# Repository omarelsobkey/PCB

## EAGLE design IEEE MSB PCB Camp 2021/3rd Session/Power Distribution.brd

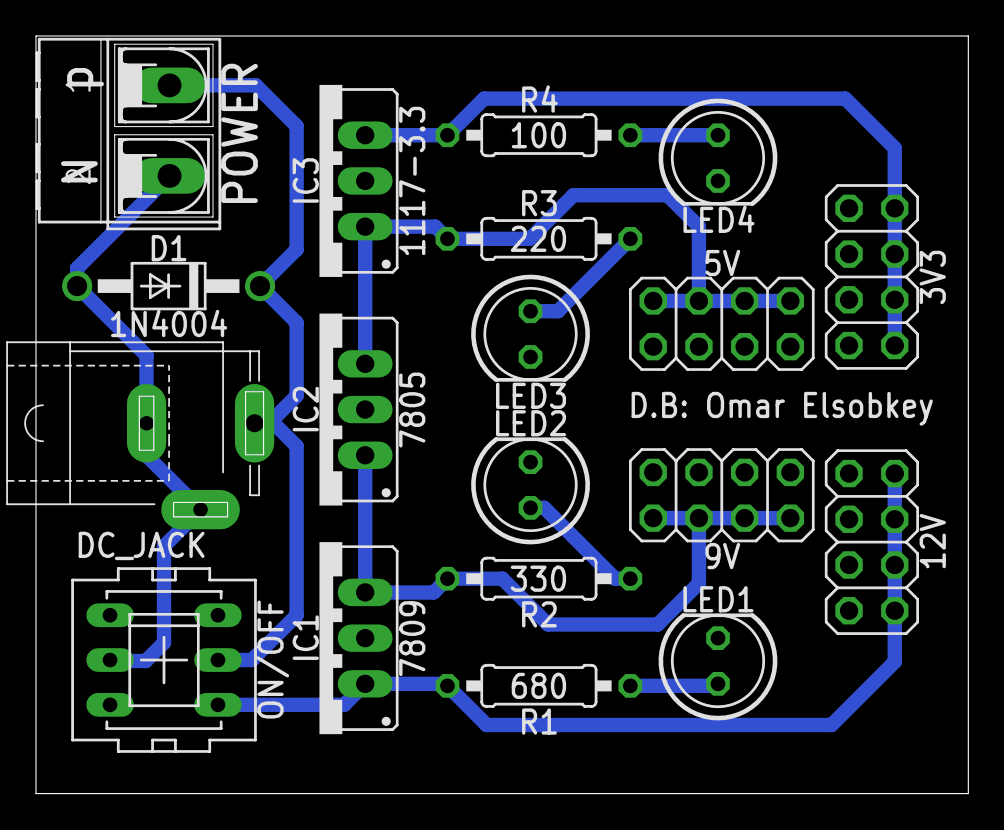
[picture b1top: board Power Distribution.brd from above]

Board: 2 copper layers, 51.8 x 42.1 mm, 19 parts (0 on the bottom side), 11 nets.

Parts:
3V3, 5V, 9V, 12V: 2X04
D1: 1N4004; DO41-10
DC_JACK: SPC4077
IC1: 7809; 78XXS
IC2: 7805; 78XXS
IC3: 1117-3.3; 78XXS
LED1, LED2, LED3, LED4: LED5MM
ON/OFF: PVA2R
POWER: AK500/2-H
R1: 680; 0207/10
R2: 330; 0207/10
R3: 220; 0207/10
R4: 100; 0207/10

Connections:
+: D1.C, DC_JACK.3, ON/OFF.2, POWER.1
+3V3: 3V3.2, 3V3.4, 3V3.6, 3V3.8, IC3.OUT, R4.2
+5V: 5V.2, 5V.4, 5V.6, 5V.8, IC2.OUT, IC3.IN, R3.2
+9V: 9V.2, 9V.4, 9V.6, 9V.8, IC1.OUT, IC2.IN, R2.2
+12V: 12V.2, 12V.4, 12V.6, 12V.8, IC1.IN, ON/OFF.1, R1.2
-: D1.A, DC_JACK.1, DC_JACK.2, ON/OFF.5, POWER.2
GND: 3V3.1, 3V3.3, 3V3.5, 3V3.7, 5V.1, 5V.3, 5V.5, 5V.7, 9V.1, 9V.3, 9V.5, 9V.7, 12V.1, 12V.3, 12V.5, 12V.7, IC1.GND, IC2.GND, IC3.GND, LED1.K, LED2.K, LED3.K, LED4.K, ON/OFF.4
unnamed: LED1.A, R1.1
unnamed: LED2.A, R2.1
unnamed: LED3.A, R3.1
unnamed: LED4.A, R4.1

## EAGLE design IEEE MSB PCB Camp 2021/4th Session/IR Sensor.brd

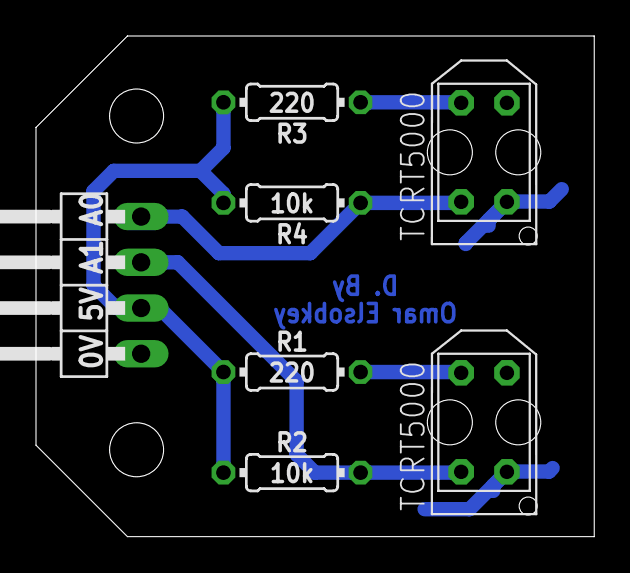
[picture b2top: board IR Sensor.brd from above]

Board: 2 copper layers, 31.0 x 27.8 mm, 7 parts (0 on the bottom side), 6 nets.

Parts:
JP1: 1X04/90
R1, R3: 220; 0204/7
R2, R4: 10k; 0204/7
SENS-1, SENS-2: TCRT5000; 5000

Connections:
+5V: JP1.2, R1.2, R2.2, R3.2, R4.2
A0: JP1.4, R4.1, SENS-2.P$1
A1: JP1.3, R2.1, SENS-1.P$1
GND: JP1.1, SENS-1.P$2, SENS-1.P$4, SENS-2.P$2, SENS-2.P$4
unnamed: R1.1, SENS-1.P$3
unnamed: R3.1, SENS-2.P$3

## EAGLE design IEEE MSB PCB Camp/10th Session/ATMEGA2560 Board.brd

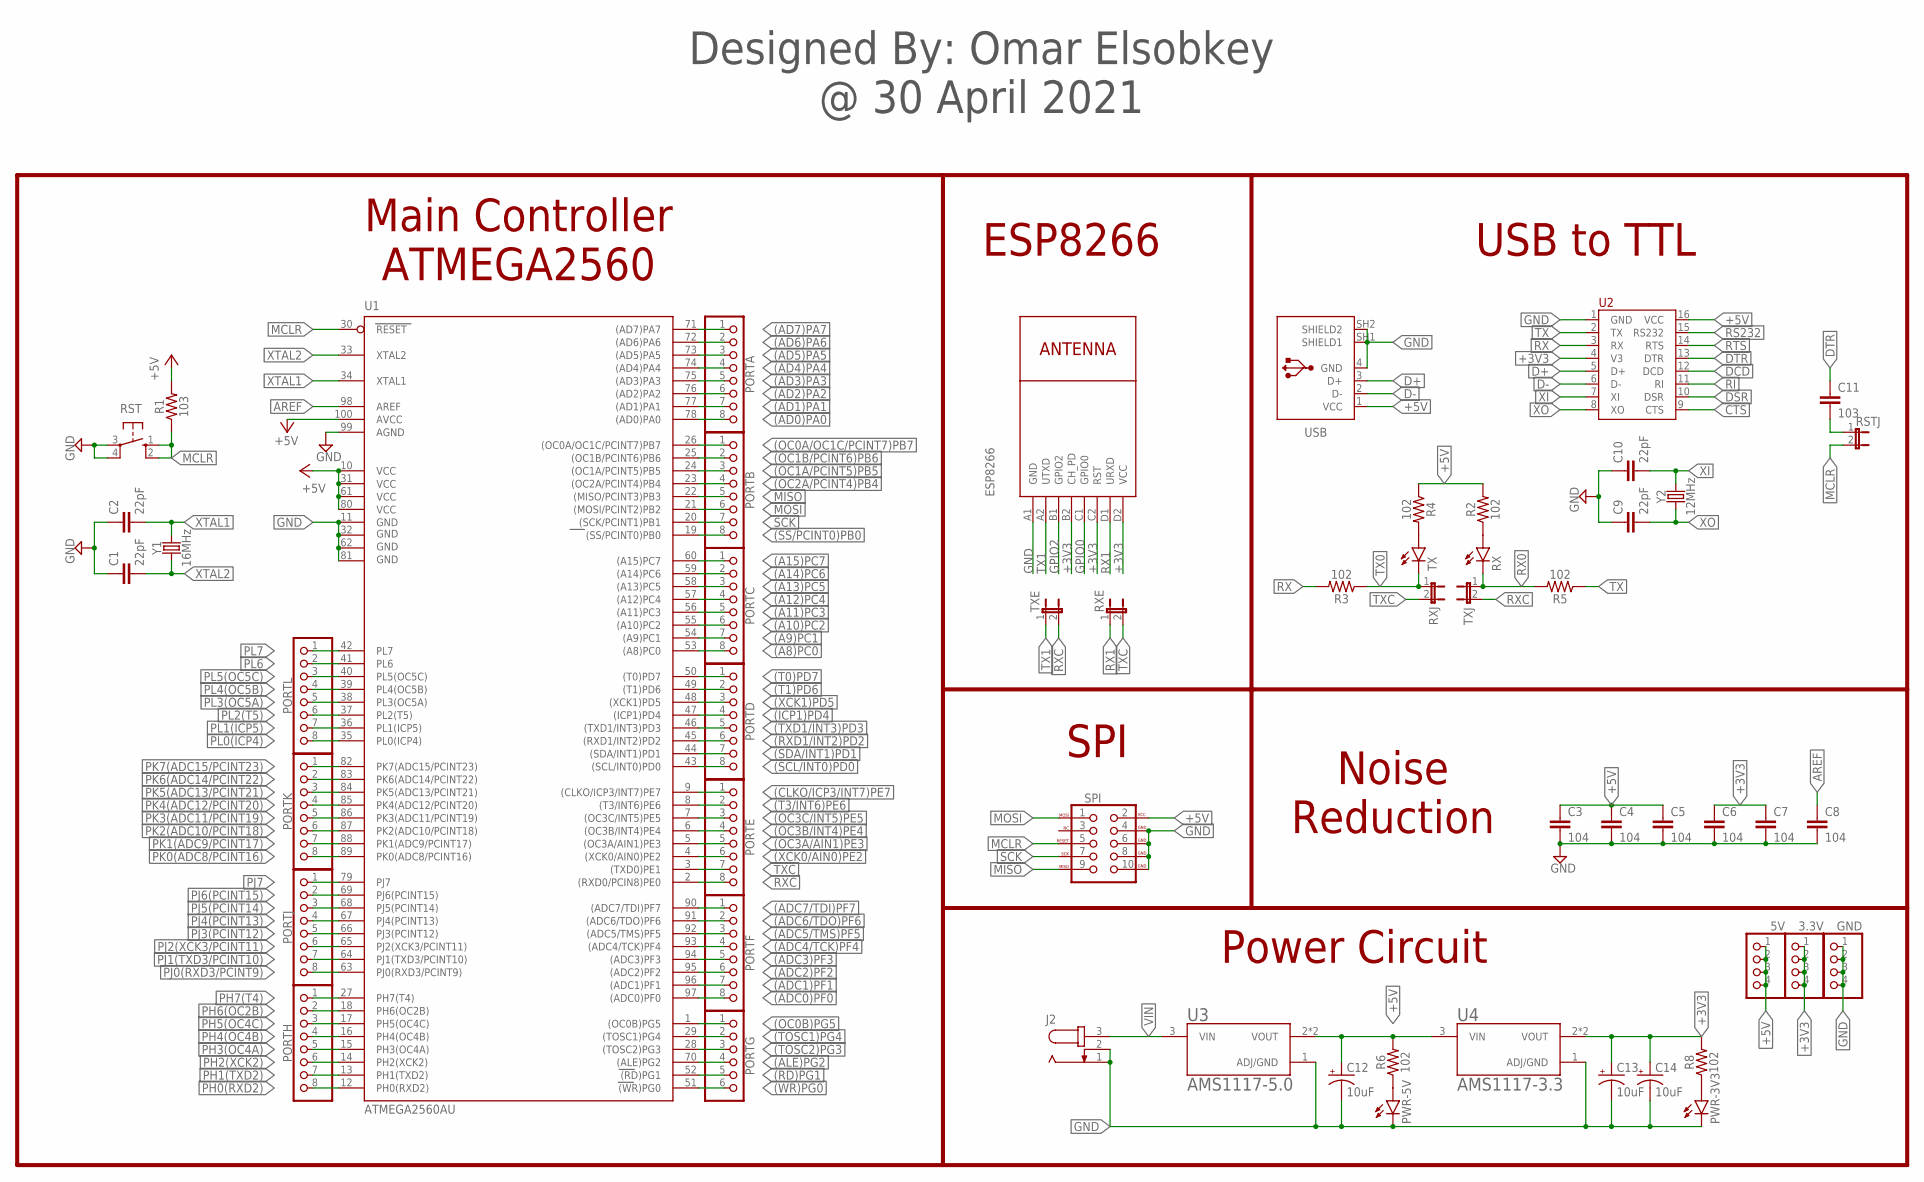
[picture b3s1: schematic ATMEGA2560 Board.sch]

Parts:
3.3V, 5V: PINHD-1X4; 1X04
C1, C2, C9, C10: 22pF; CAP-PTH-2.54
C3, C4, C5, C6, C7, C8: 104; CAP-PTH-2.54
C11: 103; CAP-PTH-2.54
C12, C13, C14: 10uF; CPOL-RADIAL-2.5MM-5MM-KIT
ESP8266: WIRELESS-WIFI-ESP-01
GND: PINHD-1X4; 1X04
J2: JACK-PLUG0; SPC4077
PORTA: PINHD-1X8; 1X08
PORTB: PINHD-1X8; 1X08
PORTC: PINHD-1X8; 1X08
PORTD: PINHD-1X8; 1X08
PORTE: PINHD-1X8; 1X08
PORTF: PINHD-1X8; 1X08
PORTG: PINHD-1X6; 1X06
PORTH: PINHD-1X8; 1X08
PORTJ: PINHD-1X8; 1X08
PORTK: PINHD-1X8; 1X08
PORTL: PINHD-1X8; 1X08
PWR-3V3, PWR-5V: LEDCHIP-LED0805; CHIP-LED0805
R1: 103; 1206
R2, R3, R4, R5, R6, R8: 102; 1206
RST: 10-XX; B3F-10XX
RSTJ: JP1E; JP1
RX: LEDCHIP-LED0805; CHIP-LED0805
RXE: JP1E; JP1
RXJ: JP1E; JP1
SPI: AVR_SPI_PROG_5X2LOCK; 2X5-SHROUDED_LOCK
TX: LEDCHIP-LED0805; CHIP-LED0805
TXE: JP1E; JP1
TXJ: JP1E; JP1
U1: ATMEGA2560AU; TQFP100
U2: CH340G; SOP-16
U3: AMS1117-5.0
U4: AMS1117-3.3; AMS1117-5.0
USB: 61729-1011; 61729-1011BLF
Y1: 16MHz; HC49U
Y2: 12MHz; HC49U

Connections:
(A8)PC0: PORTC.8, U1.53 ((A8)PC0)
(A9)PC1: PORTC.7, U1.54 ((A9)PC1)
(A10)PC2: PORTC.6, U1.55 ((A10)PC2)
(A11)PC3: PORTC.5, U1.56 ((A11)PC3)
(A12)PC4: PORTC.4, U1.57 ((A12)PC4)
(A13)PC5: PORTC.3, U1.58 ((A13)PC5)
(A14)PC6: PORTC.2, U1.59 ((A14)PC6)
(A15)PC7: PORTC.1, U1.60 ((A15)PC7)
(AD0)PA0: PORTA.8, U1.78 ((AD0)PA0)
(AD1)PA1: PORTA.7, U1.77 ((AD1)PA1)
(AD2)PA2: PORTA.6, U1.76 ((AD2)PA2)
(AD3)PA3: PORTA.5, U1.75 ((AD3)PA3)
(AD4)PA4: PORTA.4, U1.74 ((AD4)PA4)
(AD5)PA5: PORTA.3, U1.73 ((AD5)PA5)
(AD6)PA6: PORTA.2, U1.72 ((AD6)PA6)
(AD7)PA7: PORTA.1, U1.71 ((AD7)PA7)
(ADC0)PF0: PORTF.8, U1.97 ((ADC0)PF0)
(ADC1)PF1: PORTF.7, U1.96 ((ADC1)PF1)
(ADC2)PF2: PORTF.6, U1.95 ((ADC2)PF2)
(ADC3)PF3: PORTF.5, U1.94 ((ADC3)PF3)
(ADC4/TCK)PF4: PORTF.4, U1.93 ((ADC4/TCK)PF4)
(ADC5/TMS)PF5: PORTF.3, U1.92 ((ADC5/TMS)PF5)
(ADC6/TDO)PF6: PORTF.2, U1.91 ((ADC6/TDO)PF6)
(ADC7/TDI)PF7: PORTF.1, U1.90 ((ADC7/TDI)PF7)
(ALE)PG2: PORTG.4, U1.70 ((ALE)PG2)
(CLKO/ICP3/INT7)PE7: PORTE.1, U1.9 ((CLKO/ICP3/INT7)PE7)
(ICP1)PD4: PORTD.4, U1.47 ((ICP1)PD4)
(OC0A/OC1C/PCINT7)PB7: PORTB.1, U1.26 ((OC0A/OC1C/PCINT7)PB7)
(OC0B)PG5: PORTG.1, U1.1 ((OC0B)PG5)
(OC1A/PCINT5)PB5: PORTB.3, U1.24 ((OC1A/PCINT5)PB5)
(OC1B/PCINT6)PB6: PORTB.2, U1.25 ((OC1B/PCINT6)PB6)
(OC2A/PCINT4)PB4: PORTB.4, U1.23 ((OC2A/PCINT4)PB4)
(OC3A/AIN1)PE3: PORTE.5, U1.5 ((OC3A/AIN1)PE3)
(OC3B/INT4)PE4: PORTE.4, U1.6 ((OC3B/INT4)PE4)
(OC3C/INT5)PE5: PORTE.3, U1.7 ((OC3C/INT5)PE5)
(RD)PG1: PORTG.5, U1.52 ((RD)PG1)
(RXD1/INT2)PD2: PORTD.6, U1.45 ((RXD1/INT2)PD2)
(SCL/INT0)PD0: PORTD.8, U1.43 ((SCL/INT0)PD0)
(SDA/INT1)PD1: PORTD.7, U1.44 ((SDA/INT1)PD1)
(SS/PCINT0)PB0: PORTB.8, U1.19 ((SS/PCINT0)PB0)
(T0)PD7: PORTD.1, U1.50 ((T0)PD7)
(T1)PD6: PORTD.2, U1.49 ((T1)PD6)
(T3/INT6)PE6: PORTE.2, U1.8 ((T3/INT6)PE6)
(TOSC1)PG4: PORTG.2, U1.29 ((TOSC1)PG4)
(TOSC2)PG3: PORTG.3, U1.28 ((TOSC2)PG3)
(TXD1/INT3)PD3: PORTD.5, U1.46 ((TXD1/INT3)PD3)
(WR)PG0: PORTG.6, U1.51 ((WR)PG0)
(XCK0/AIN0)PE2: PORTE.6, U1.4 ((XCK0/AIN0)PE2)
(XCK1)PD5: PORTD.3, U1.48 ((XCK1)PD5)
+3V3: 3.3V.1, 3.3V.2, 3.3V.3, 3.3V.4, C6.1, C7.1, C13.1 (+), C14.1 (+), ESP8266.B2 (CH_PD), ESP8266.C2 (RST), ESP8266.D2 (VCC), R8.2, U2.4 (V3), U4.2 (VOUT), U4.4 (VOUT)
+5V: 5V.1, 5V.2, 5V.3, 5V.4, C3.1, C4.1, C5.1, C12.1 (+), R1.2, R2.2, R4.1, R6.2, SPI.2 (VCC), U1.10 (VCC), U1.31 (VCC1), U1.61 (VCC2), U1.80 (VCC3), U1.100 (AVCC), U2.16 (VCC), U3.2 (VOUT), U3.4 (VOUT), U4.3 (VIN), USB.1 (VCC)
AREF: C8.1, U1.98 (AREF)
CTS: U2.9 (CTS)
D+: U2.5 (D+), USB.3 (D+)
D-: U2.6 (D-), USB.2 (D-)
DCD: U2.12 (DCD)
DSR: U2.10 (DSR)
DTR: C11.1, U2.13 (DTR)
GND: C1.1, C2.1, C3.2, C4.2, C5.2, C6.2, C7.2, C8.2, C9.1, C10.1, C12.2 (-), C13.2 (-), C14.2 (-), ESP8266.A1 (GND), GND.1, GND.2, GND.3, GND.4, J2.1, J2.2, PWR-3V3.C, PWR-5V.C, RST.3, RST.4 (P1), SPI.4 (GND), SPI.6 (GND), SPI.8 (GND), SPI.10 (GND), U1.11 (GND), U1.32 (GND1), U1.62 (GND2), U1.81 (GND3), U1.99 (AGND), U2.1 (GND), U3.1 (ADJ/GND), U4.1 (ADJ/GND), USB.4 (GND), USB.SH1 (SHIELD1), USB.SH2 (SHIELD2)
GPIO0: ESP8266.C1 (GPIO0)
GPIO2: ESP8266.B1 (GPIO2)
MCLR: R1.1, RST.1 (S), RST.2 (S1), RSTJ.2, SPI.5 (RESET), U1.30 (RESET)
MISO: PORTB.5, SPI.9 (MISO), U1.22 ((MISO/PCINT3)PB3)
MOSI: PORTB.6, SPI.1 (MOSI), U1.21 ((MOSI/PCINT2)PB2)
unnamed: R2.1, RX.A
unnamed: R4.2, TX.A
unnamed: PWR-5V.A, R6.1
unnamed: PWR-3V3.A, R8.1
unnamed: C11.2, RSTJ.1
PH0(RXD2): PORTH.8, U1.12 (PH0(RXD2))
PH1(TXD2): PORTH.7, U1.13 (PH1(TXD2))
PH2(XCK2): PORTH.6, U1.14 (PH2(XCK2))
PH3(OC4A): PORTH.5, U1.15 (PH3(OC4A))
PH4(OC4B): PORTH.4, U1.16 (PH4(OC4B))
PH5(OC4C): PORTH.3, U1.17 (PH5(OC4C))
PH6(OC2B): PORTH.2, U1.18 (PH6(OC2B))
PH7(T4): PORTH.1, U1.27 (PH7(T4))
PJ0(RXD3/PCINT9): PORTJ.8, U1.63 (PJ0(RXD3/PCINT9))
PJ1(TXD3/PCINT10): PORTJ.7, U1.64 (PJ1(TXD3/PCINT10))
PJ2(XCK3/PCINT11): PORTJ.6, U1.65 (PJ2(XCK3/PCINT11))
PJ3(PCINT12): PORTJ.5, U1.66 (PJ3(PCINT12))
PJ4(PCINT13): PORTJ.4, U1.67 (PJ4(PCINT13))
PJ5(PCINT14): PORTJ.3, U1.68 (PJ5(PCINT14))
PJ6(PCINT15): PORTJ.2, U1.69 (PJ6(PCINT15))
PJ7: PORTJ.1, U1.79 (PJ7)
PK0(ADC8/PCINT16): PORTK.8, U1.89 (PK0(ADC8/PCINT16))
PK1(ADC9/PCINT17): PORTK.7, U1.88 (PK1(ADC9/PCINT17))
PK2(ADC10/PCINT18): PORTK.6, U1.87 (PK2(ADC10/PCINT18))
PK3(ADC11/PCINT19): PORTK.5, U1.86 (PK3(ADC11/PCINT19))
PK4(ADC12/PCINT20): PORTK.4, U1.85 (PK4(ADC12/PCINT20))
PK5(ADC13/PCINT21): PORTK.3, U1.84 (PK5(ADC13/PCINT21))
PK6(ADC14/PCINT22): PORTK.2, U1.83 (PK6(ADC14/PCINT22))
PK7(ADC15/PCINT23): PORTK.1, U1.82 (PK7(ADC15/PCINT23))
PL0(ICP4): PORTL.8, U1.35 (PL0(ICP4))
PL1(ICP5): PORTL.7, U1.36 (PL1(ICP5))
PL2(T5): PORTL.6, U1.37 (PL2(T5))
PL3(OC5A): PORTL.5, U1.38 (PL3(OC5A))
PL4(OC5B): PORTL.4, U1.39 (PL4(OC5B))
PL5(OC5C): PORTL.3, U1.40 (PL5(OC5C))
PL6: PORTL.2, U1.41 (PL6)
PL7: PORTL.1, U1.42 (PL7)
RI: U2.11 (RI)
RS232: U2.15 (RS232)
RTS: U2.14 (RTS)
RX: R3.2, U2.3 (RX)
RX0: R5.2, RX.C, TXJ.1
RX1: ESP8266.D1 (URXD), RXE.1
RXC: PORTE.8, TXE.2, TXJ.2, U1.2 ((RXD0/PCIN8)PE0)
SCK: PORTB.7, SPI.7 (SCK), U1.20 ((SCK/PCINT1)PB1)
TX: R5.1, U2.2 (TX)
TX0: R3.1, RXJ.1, TX.C
TX1: ESP8266.A2 (UTXD), TXE.1
TXC: PORTE.7, RXE.2, RXJ.2, U1.3 ((TXD0)PE1)
VIN: J2.3, U3.3 (VIN)
XI: C10.2, U2.7 (XI), Y2.2
XO: C9.2, U2.8 (XO), Y2.1
XTAL1: C2.2, U1.34 (XTAL1), Y1.2
XTAL2: C1.2, U1.33 (XTAL2), Y1.1

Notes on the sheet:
Main Controller ATMEGA2560
ESP8266
USB to TTL
SPI
Noise Reduction
Power Circuit
Designed By: Omar Elsobkey @ 30 April 2021

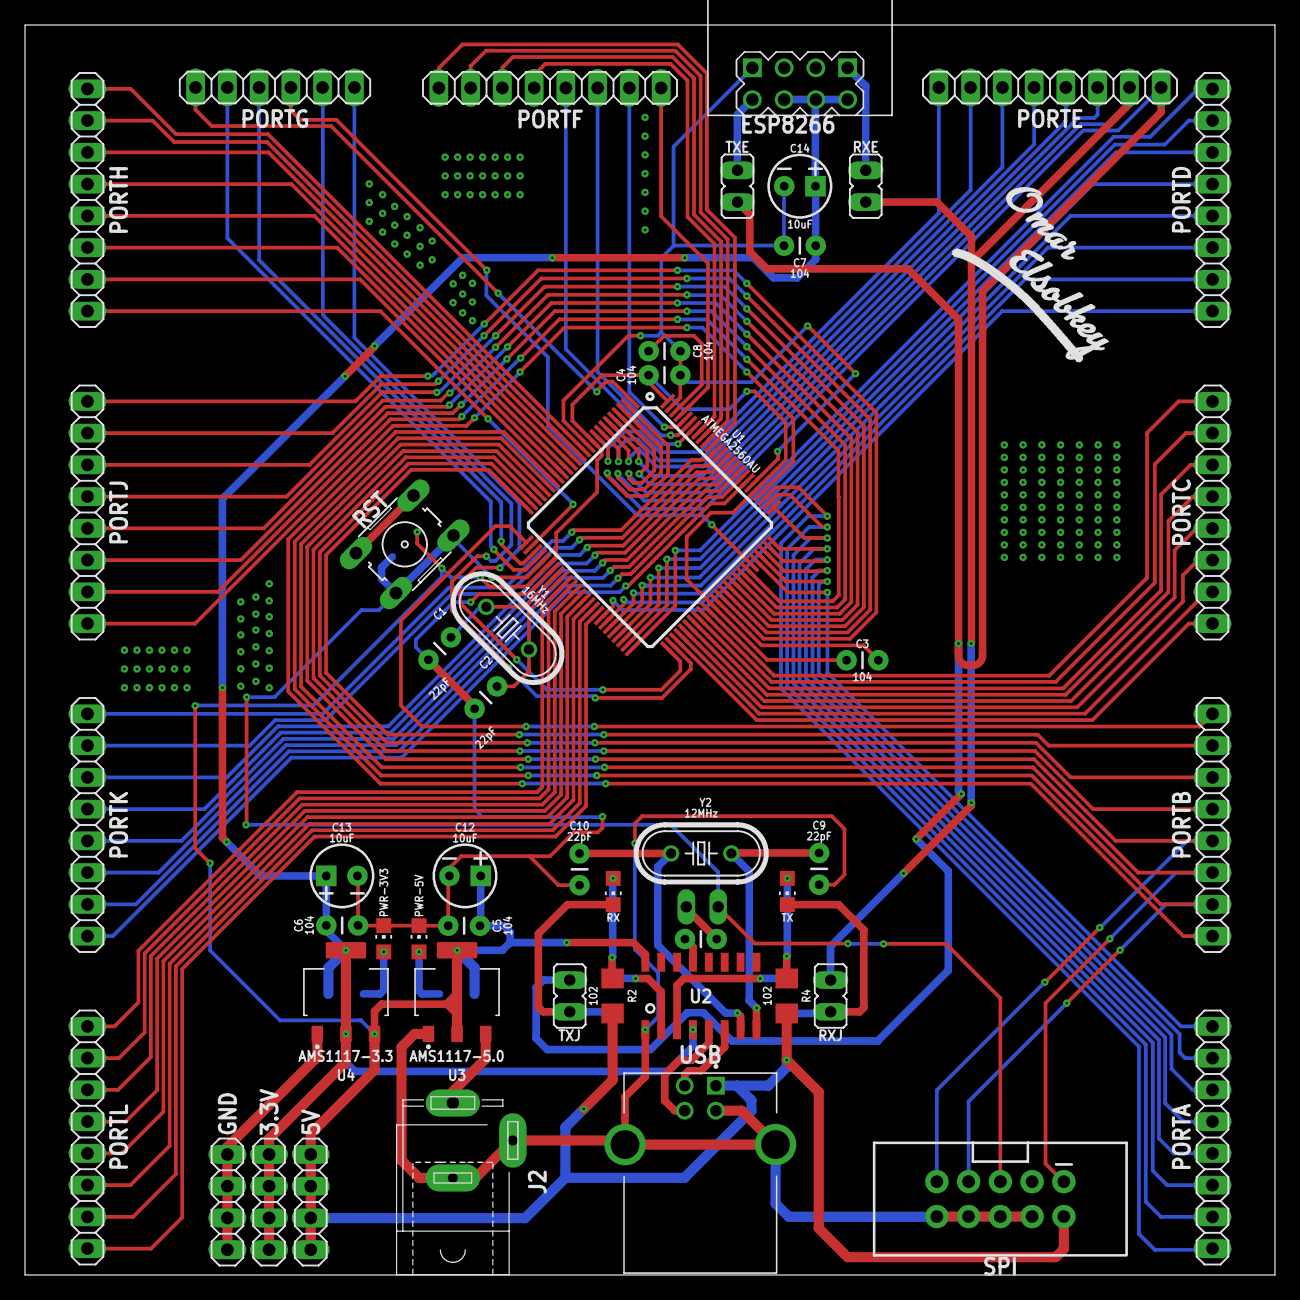
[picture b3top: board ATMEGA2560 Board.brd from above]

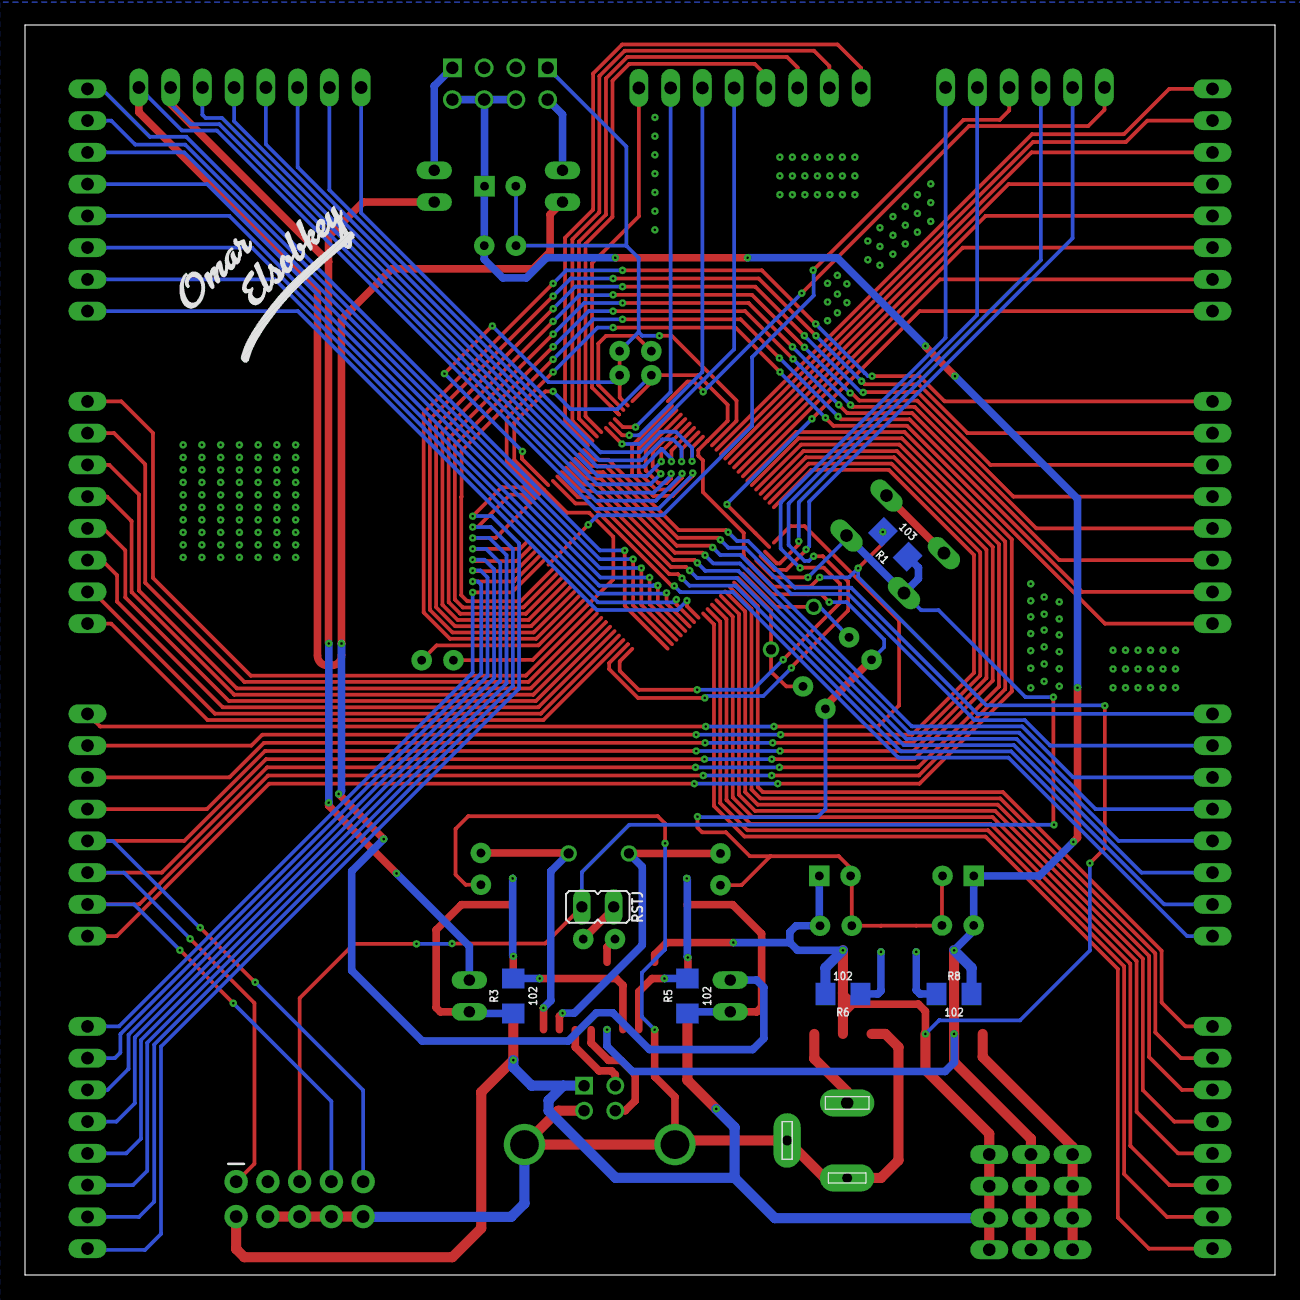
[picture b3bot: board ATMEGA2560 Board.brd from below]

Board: 2 copper layers, 100.0 x 100.0 mm, 57 parts (7 on the bottom side), 110 nets.

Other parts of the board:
U$1, U$2: OMAR_ELSOBKEY_X1

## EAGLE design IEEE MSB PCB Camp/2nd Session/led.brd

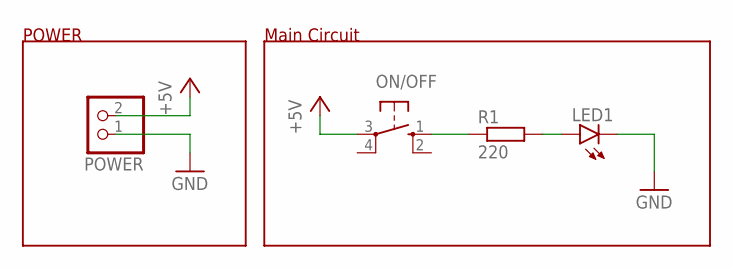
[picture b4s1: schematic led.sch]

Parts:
LED1: LED3MM
ON/OFF: 10-XX; B3F-10XX
POWER: PINHD-1X2; 1X02
R1: 220; 0204/7

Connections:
+5V: ON/OFF.3, POWER.2
GND: LED1.K (C), POWER.1
unnamed: ON/OFF.1 (S), R1.1
unnamed: LED1.A, R1.2

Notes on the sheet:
POWER
Main Circuit

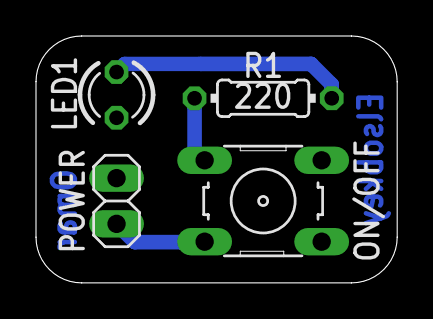
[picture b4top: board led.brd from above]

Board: 2 copper layers, 20.1 x 13.7 mm, 4 parts (0 on the bottom side), 4 nets.

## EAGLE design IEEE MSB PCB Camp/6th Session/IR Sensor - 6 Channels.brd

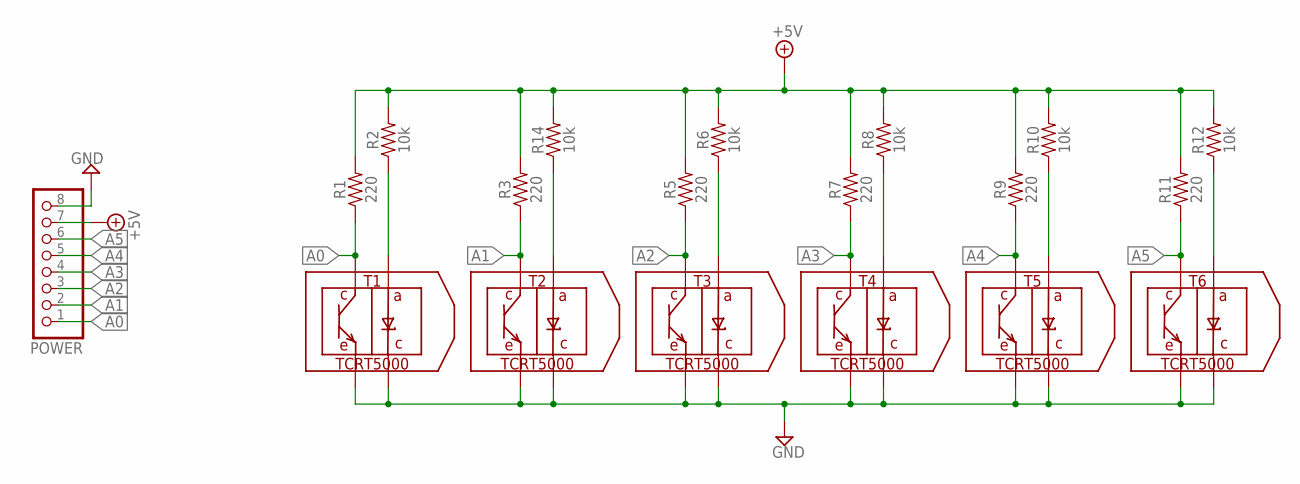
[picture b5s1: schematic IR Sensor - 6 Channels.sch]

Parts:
POWER: PINHD-1X8/90; 1X08/90
R1, R3, R5, R7, R9, R11: 220; 1206
R2, R6, R8, R10, R12, R14: 10k; 1206
T1, T2, T3, T4, T5, T6: TCRT5000; 5000

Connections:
+5V: POWER.7, R1.2, R2.2, R3.2, R5.2, R6.2, R7.2, R8.2, R9.2, R10.2, R11.2, R12.2, R14.2
A0: POWER.1, R1.1, T1.P$1
A1: POWER.2, R3.1, T2.P$1
A2: POWER.3, R5.1, T3.P$1
A3: POWER.4, R7.1, T4.P$1
A4: POWER.5, R9.1, T5.P$1
A5: POWER.6, R11.1, T6.P$1
GND: POWER.8, T1.P$2, T1.P$4, T2.P$2, T2.P$4, T3.P$2, T3.P$4, T4.P$2, T4.P$4, T5.P$2, T5.P$4, T6.P$2, T6.P$4
unnamed: R2.1, T1.P$3
unnamed: R14.1, T2.P$3
unnamed: R6.1, T3.P$3
unnamed: R12.1, T6.P$3
unnamed: R10.1, T5.P$3
unnamed: R8.1, T4.P$3

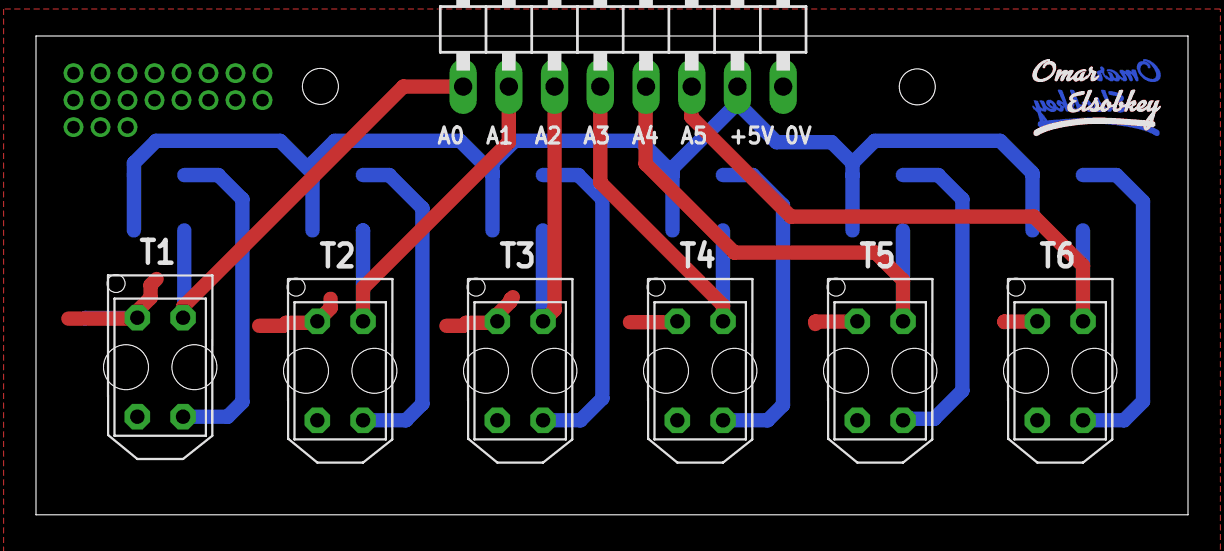
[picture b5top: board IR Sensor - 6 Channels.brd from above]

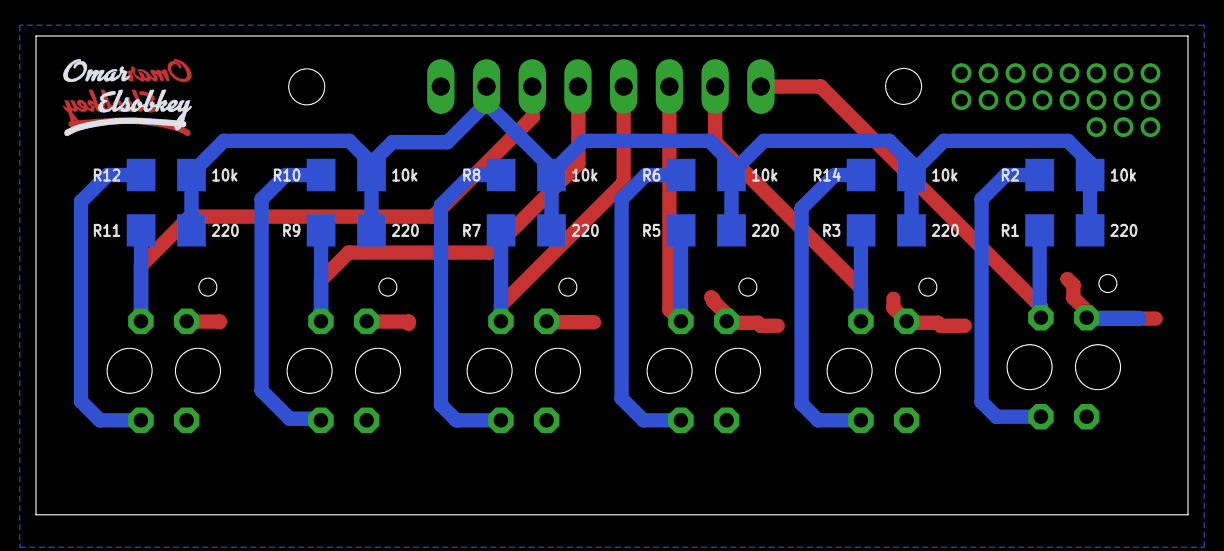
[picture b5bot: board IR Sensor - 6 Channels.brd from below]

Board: 2 copper layers, 64.0 x 26.6 mm, 23 parts (14 on the bottom side), 14 nets.

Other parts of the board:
U$1, U$2: OMAR_ELSOBKEY_X0.5_T
U$3, U$4: OMAR_ELSOBKEY_X0.5_TN

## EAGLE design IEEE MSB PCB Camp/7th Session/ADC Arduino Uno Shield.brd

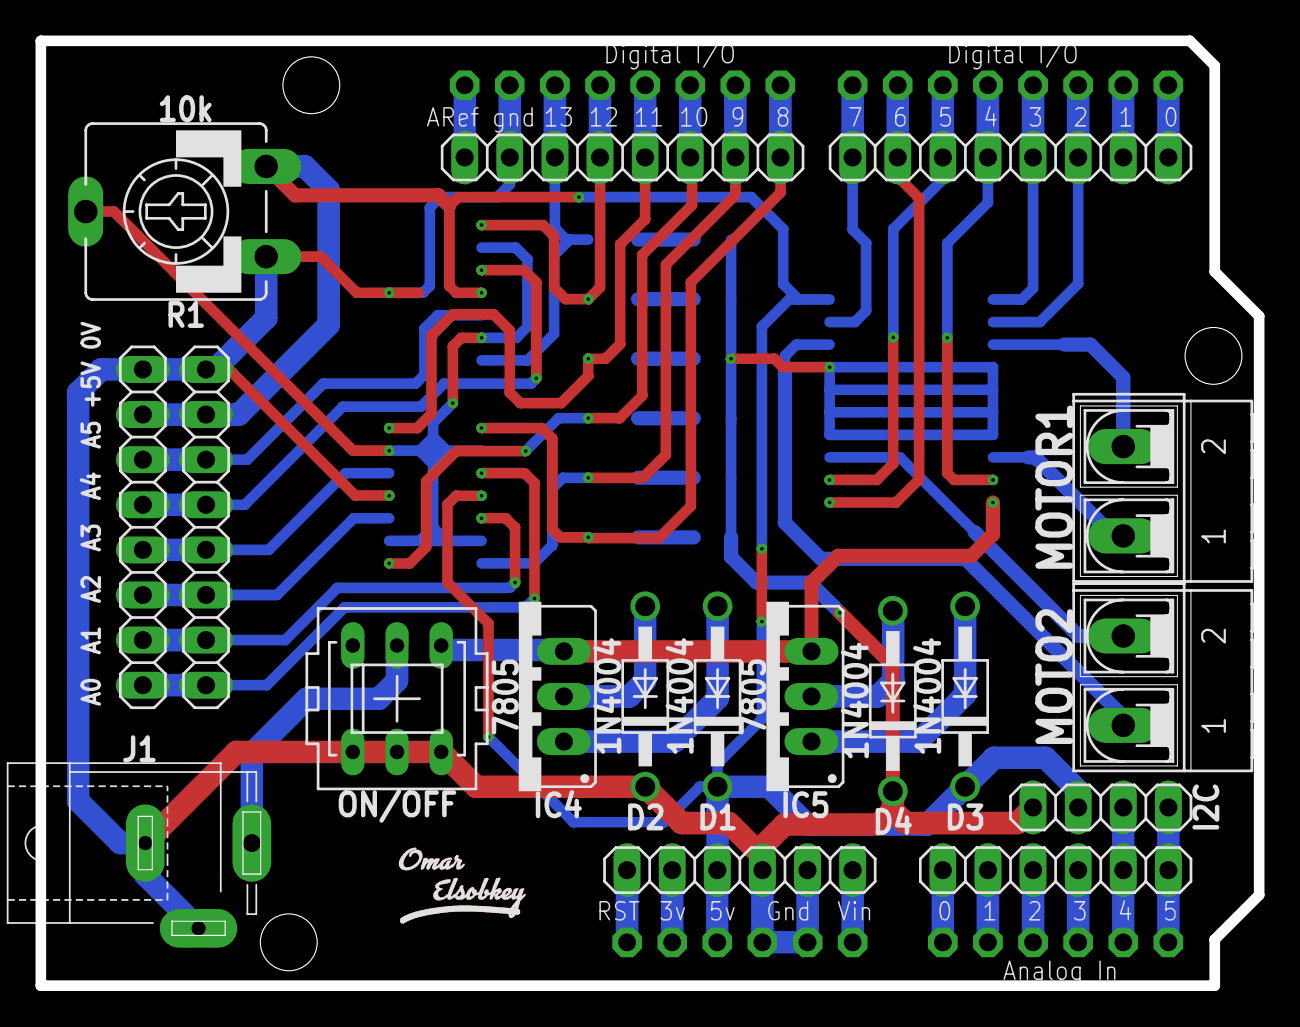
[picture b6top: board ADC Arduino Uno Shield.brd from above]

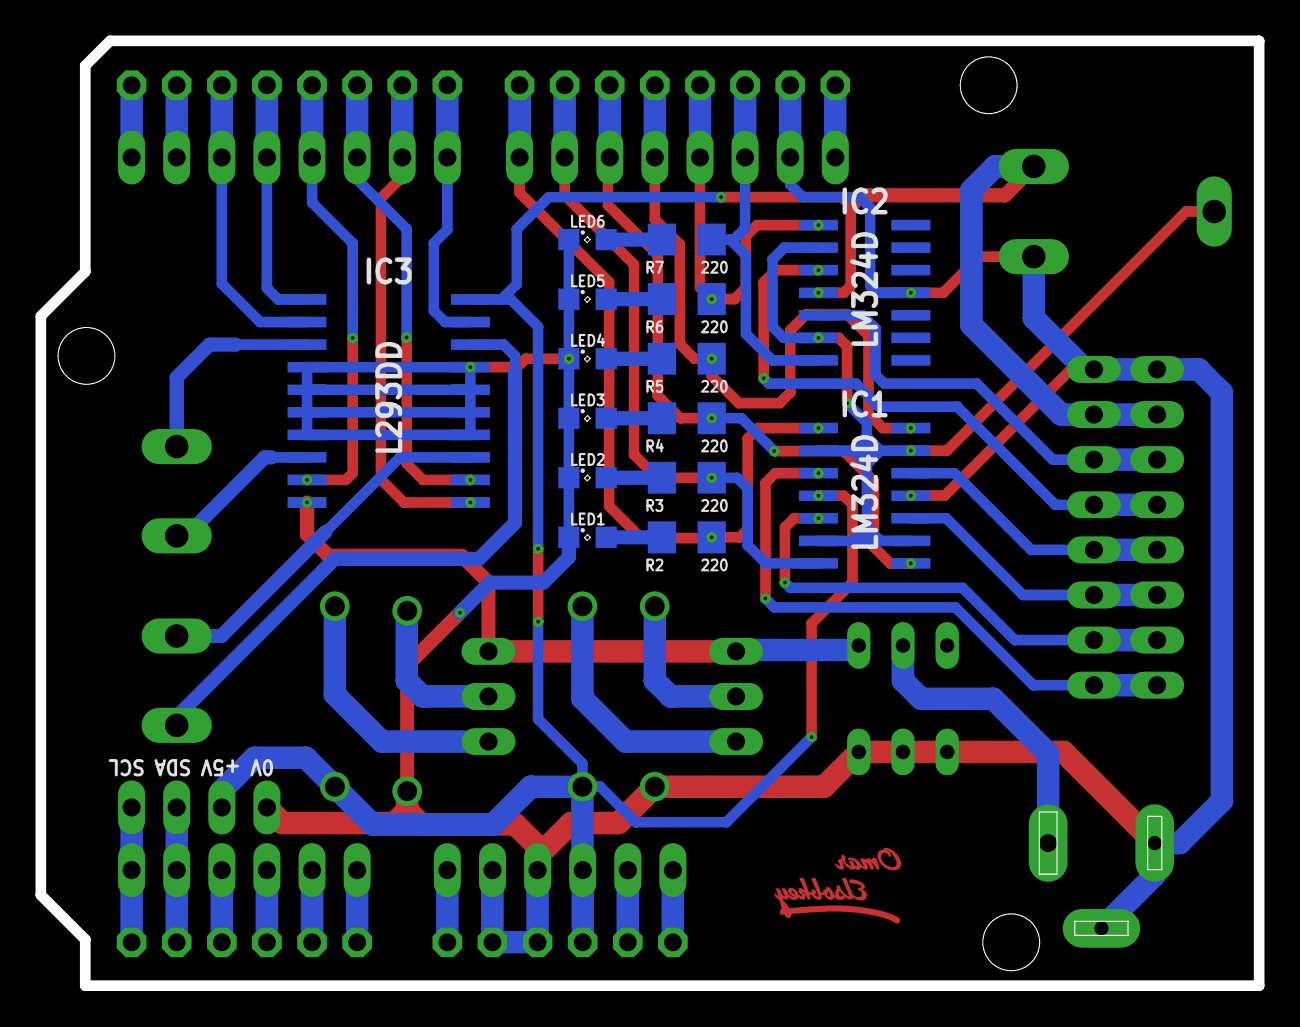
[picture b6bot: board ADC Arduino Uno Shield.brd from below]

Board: 2 copper layers, 68.6 x 53.2 mm, 35 parts (15 on the bottom side), 49 nets.

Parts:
CON1, CON2: 1X08
D1, D2, D3, D4: 1N4004; DO41-10
I2C: 1X04
IC1, IC2: LM324D; SO14
IC3: L293DD; SO20
IC4, IC5: 7805; 78XXS
J1: SPC4077
JP1, JP2: 1X06
JP3, JP4: 1X08
LED1, LED2, LED3, LED4, LED5, LED6: SML0805
MOTO2: AK500/2-H
MOTOR1: AK500/2-H
ON/OFF: PVA2R
R1: 10k; CA9V
R2, R3, R4, R5, R6, R7: 220; 1206
U$2: ARDUINO-NODIM
U$3: OMAR_ELSOBKEY_X0.5

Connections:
2: IC3.2, JP3.6, U$2.D2
3: IC3.1, JP3.5, U$2.D3
4: IC3.9, JP3.4, U$2.D4
5: IC3.12, JP3.3, U$2.D5
6: IC3.11, JP3.2, U$2.D6
7: IC3.19, JP3.1, U$2.D7
+5V: CON1.7, CON2.7, D1.C, D3.C, I2C.3, IC1.4, IC2.4, IC3.20, JP2.4, R1.E, U$2.5V
+12V: IC3.10, IC4.OUT, IC5.OUT, ON/OFF.1
A0: CON1.1, CON2.1, IC1.3
A1: CON1.2, CON2.2, IC1.5
A2: CON1.3, CON2.3, IC1.10
A3: CON1.4, CON2.4, IC1.12
A4: CON1.5, CON2.5, IC2.3
A5: CON1.6, CON2.6, IC2.5
D0: IC1.1, JP4.8, R2.2, U$2.D8
D1: IC1.7, JP4.7, R3.2, U$2.D9
D2: IC1.8, JP4.6, R4.2, U$2.D10
D3: IC1.14, JP4.5, R5.2, U$2.D11
D4: IC2.1, JP4.4, R6.2, U$2.D12
D5: IC2.7, JP4.3, R7.2, U$2.D13
GND: CON1.8, CON2.8, D2.C, D4.C, I2C.4, IC1.11, IC2.11, IC3.4, IC3.5, IC3.6, IC3.7, IC3.14, IC3.15, IC3.16, IC3.17, J1.1, J1.2, JP2.2, JP2.3, JP4.2, LED1.C, LED2.C, LED3.C, LED4.C, LED5.C, LED6.C, ON/OFF.4, ON/OFF.5, ON/OFF.6, R1.A, U$2.GND, U$2.GND1, U$2.GND2
unnamed: D1.A, IC4.IN
unnamed: JP1.3, U$2.A3
unnamed: D2.A, IC4.GND
unnamed: D3.A, IC5.IN
unnamed: D4.A, IC5.GND
unnamed: JP1.4, U$2.A2
unnamed: LED1.A, R2.1
unnamed: LED2.A, R3.1
unnamed: LED3.A, R4.1
unnamed: LED4.A, R5.1
unnamed: LED5.A, R6.1
unnamed: LED6.A, R7.1
unnamed: IC1.2, IC1.6, IC1.9, IC1.13, IC2.2, IC2.6, R1.S
unnamed: JP1.5, U$2.A1
unnamed: IC3.3, MOTOR1.2
unnamed: IC3.8, MOTOR1.1
unnamed: IC3.13, MOTO2.2
unnamed: IC3.18, MOTO2.1
unnamed: JP1.6, U$2.A0
unnamed: JP4.1, U$2.AREF
unnamed: JP3.7, U$2.D1
unnamed: JP3.8, U$2.D0
POWER: J1.3, ON/OFF.2
SCL: I2C.1, JP1.1, U$2.A5
SDA: I2C.2, JP1.2, U$2.A4
U$2_3V: JP2.5, U$2.3V
U$2_/RESET: JP2.6, U$2.RESET
U$2_VIN: JP2.1, U$2.VIN

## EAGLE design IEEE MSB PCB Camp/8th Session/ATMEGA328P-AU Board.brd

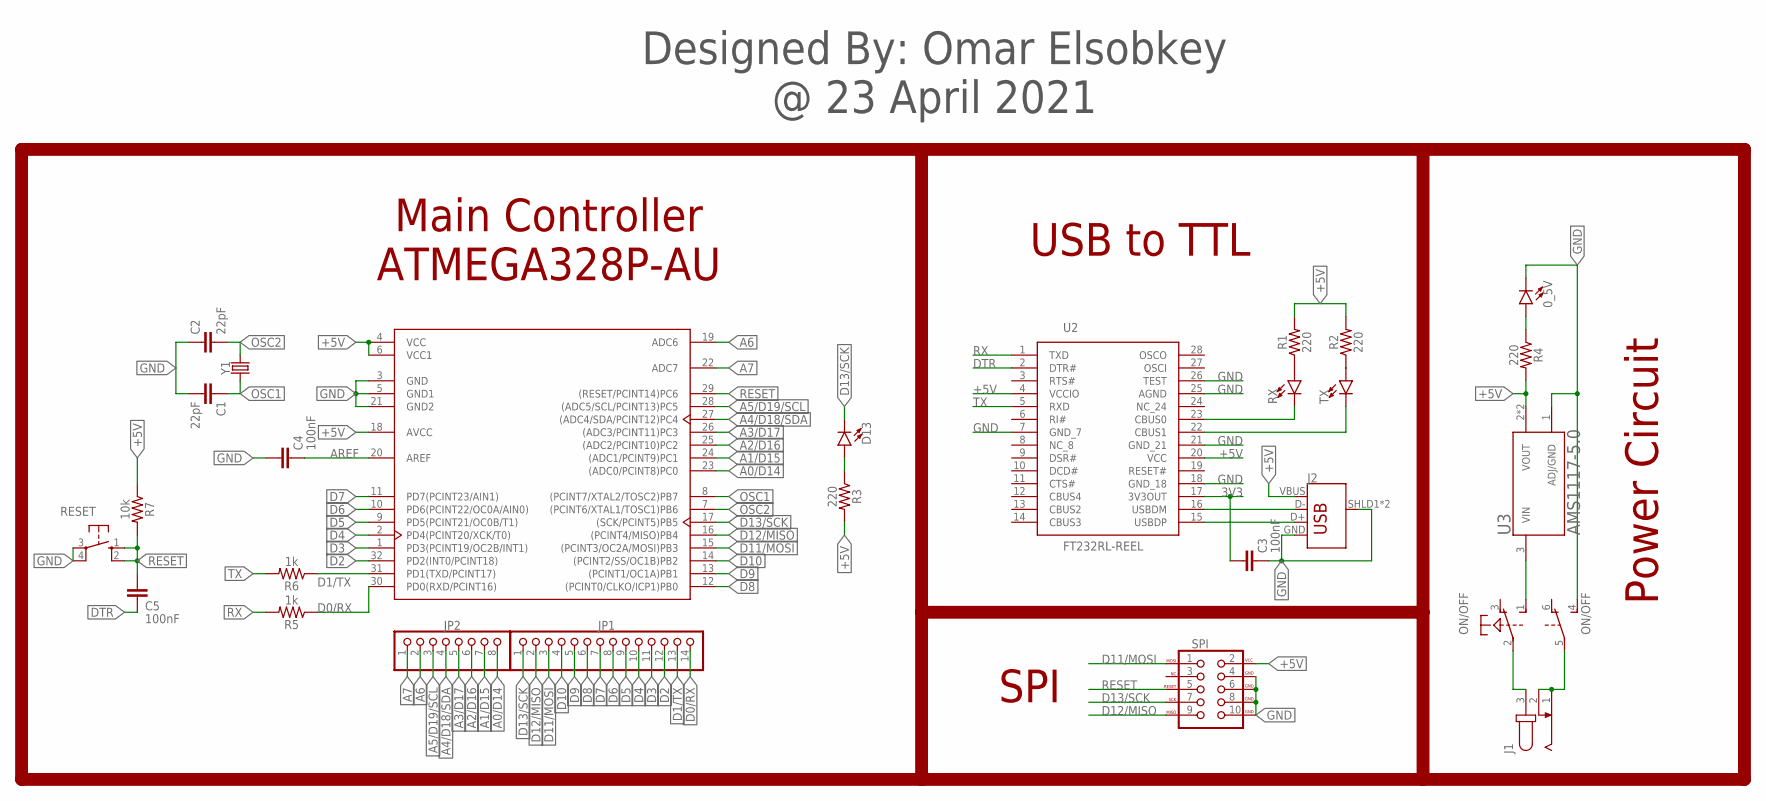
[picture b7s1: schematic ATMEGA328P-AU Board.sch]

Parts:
0_5V: LED3MM; LED_3MM
C1, C2: 22pF; CAP-PTH-2.54
C3, C4, C5: 100nF; CAP-PTH-2.54
D13: LED3MM; LED_3MM
J1: JACK-PLUG0; SPC4077
J2: USB_B_PTH; USB-B-PTH
JP1: PINHD-1X14; 1X14
JP2: PINHD-1X8; 1X08
ON/OFF: PVA2R
R1, R2, R3, R4: 220; 1206
R5, R6: 1k; 1206
R7: 10k; 1206
RESET: 10-XX; B3F-10XX
RX: LED3MM; LED_3MM
SPI: AVR_SPI_PROG_5X2LOCK; 2X5-SHROUDED_LOCK
TX: LED3MM; LED_3MM
U1: ATMEGA328P-AU; TQFP-32
U2: FT232RL-REEL; SSOP-28
U3: AMS1117-5.0
Y1: CRYSTALPTH-HC49UV; HC49U

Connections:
3V3: C3.1, U2.17 (3V3OUT)
+5V: J2.VBUS, R1.2, R2.2, R3.2, R4.2, R7.1, SPI.2 (VCC), U1.4 (VCC), U1.6 (VCC1), U1.18 (AVCC), U2.4 (VCCIO), U2.20 (VCC), U3.2 (VOUT), U3.4 (VOUT)
A0/D14: JP2.8, U1.23 ((ADC0/PCINT8)PC0)
A1/D15: JP2.7, U1.24 ((ADC1/PCINT9)PC1)
A2/D16: JP2.6, U1.25 ((ADC2/PCINT10)PC2)
A3/D17: JP2.5, U1.26 ((ADC3/PCINT11)PC3)
A4/D18/SDA: JP2.4, U1.27 ((ADC4/SDA/PCINT12)PC4)
A5/D19/SCL: JP2.3, U1.28 ((ADC5/SCL/PCINT13)PC5)
A6: JP2.2, U1.19 (ADC6)
A7: JP2.1, U1.22 (ADC7)
AREF: C4.2, U1.20 (AREF)
CBUS0: RX.K (C), U2.23 (CBUS0)
CBUS1: TX.K (C), U2.22 (CBUS1)
D0/RX: JP1.14, R5.1, U1.30 (PD0(RXD/PCINT16))
D1/TX: JP1.13, R6.1, U1.31 (PD1(TXD/PCINT17))
D2: JP1.12, U1.32 (PD2(INT0/PCINT18))
D3: JP1.11, U1.1 (PD3(PCINT19/OC2B/INT1))
D4: JP1.10, U1.2 (PD4(PCINT20/XCK/T0))
D5: JP1.9, U1.9 (PD5(PCINT21/OC0B/T1))
D6: JP1.8, U1.10 (PD6(PCINT22/OC0A/AIN0))
D7: JP1.7, U1.11 (PD7(PCINT23/AIN1))
D8: JP1.6, U1.12 ((PCINT0/CLKO/ICP1)PB0)
D9: JP1.5, U1.13 ((PCINT1/OC1A)PB1)
D10: JP1.4, U1.14 ((PCINT2/SS/OC1B)PB2)
D11/MOSI: JP1.3, SPI.1 (MOSI), U1.15 ((PCINT3/OC2A/MOSI)PB3)
D12/MISO: JP1.2, SPI.9 (MISO), U1.16 ((PCINT4/MISO)PB4)
D13/SCK: D13.K (C), JP1.1, SPI.7 (SCK), U1.17 ((SCK/PCINT5)PB5)
DTR: C5.2, U2.2 (DTR#)
GND: 0_5V.K (C), C1.2, C2.1, C3.2, C4.1, J2.GND, J2.SHLD1 (SHIELD), J2.SHLD2 (SHIELD), ON/OFF.4 (S), RESET.3, RESET.4 (P1), SPI.4 (GND), SPI.6 (GND), SPI.8 (GND), SPI.10 (GND), U1.3 (GND), U1.5 (GND1), U1.21 (GND2), U2.7 (GND_7), U2.18 (GND_18), U2.21 (GND_21), U2.25 (AGND), U2.26 (TEST), U3.1 (ADJ/GND)
unnamed: R1.1, RX.A
unnamed: R2.1, TX.A
unnamed: J1.3, ON/OFF.2
unnamed: D13.A, R3.1
unnamed: J2.D-, U2.16 (USBDM)
unnamed: J1.1, J1.2, ON/OFF.5
unnamed: ON/OFF.1 (S), U3.3 (VIN)
unnamed: 0_5V.A, R4.1
OSC1: C1.1, U1.8 ((PCINT7/XTAL2/TOSC2)PB7), Y1.1
OSC2: C2.2, U1.7 ((PCINT6/XTAL1/TOSC1)PB6), Y1.2
RESET: C5.1, R7.2, RESET.1 (S), RESET.2 (S1), SPI.5 (RESET), U1.29 ((RESET/PCINT14)PC6)
RX: R5.2, U2.1 (TXD)
TX: R6.2, U2.5 (RXD)
USBDP: J2.D+, U2.15 (USBDP)

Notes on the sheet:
Main Controller ATMEGA328P-AU
SPI
USB to TTL
Power Circuit
Designed By: Omar Elsobkey @ 23 April 2021

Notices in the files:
parts and their libraries:
SparkFun-Capacitors: Licensing: Creative Commons ShareAlike 4.0 International - https://creativecommons.org/licenses/by-sa/4.0
Modules: Released under the Creative Commons Attribution 4.0 International License: http://creativecommons.org/licenses/by/4.0
